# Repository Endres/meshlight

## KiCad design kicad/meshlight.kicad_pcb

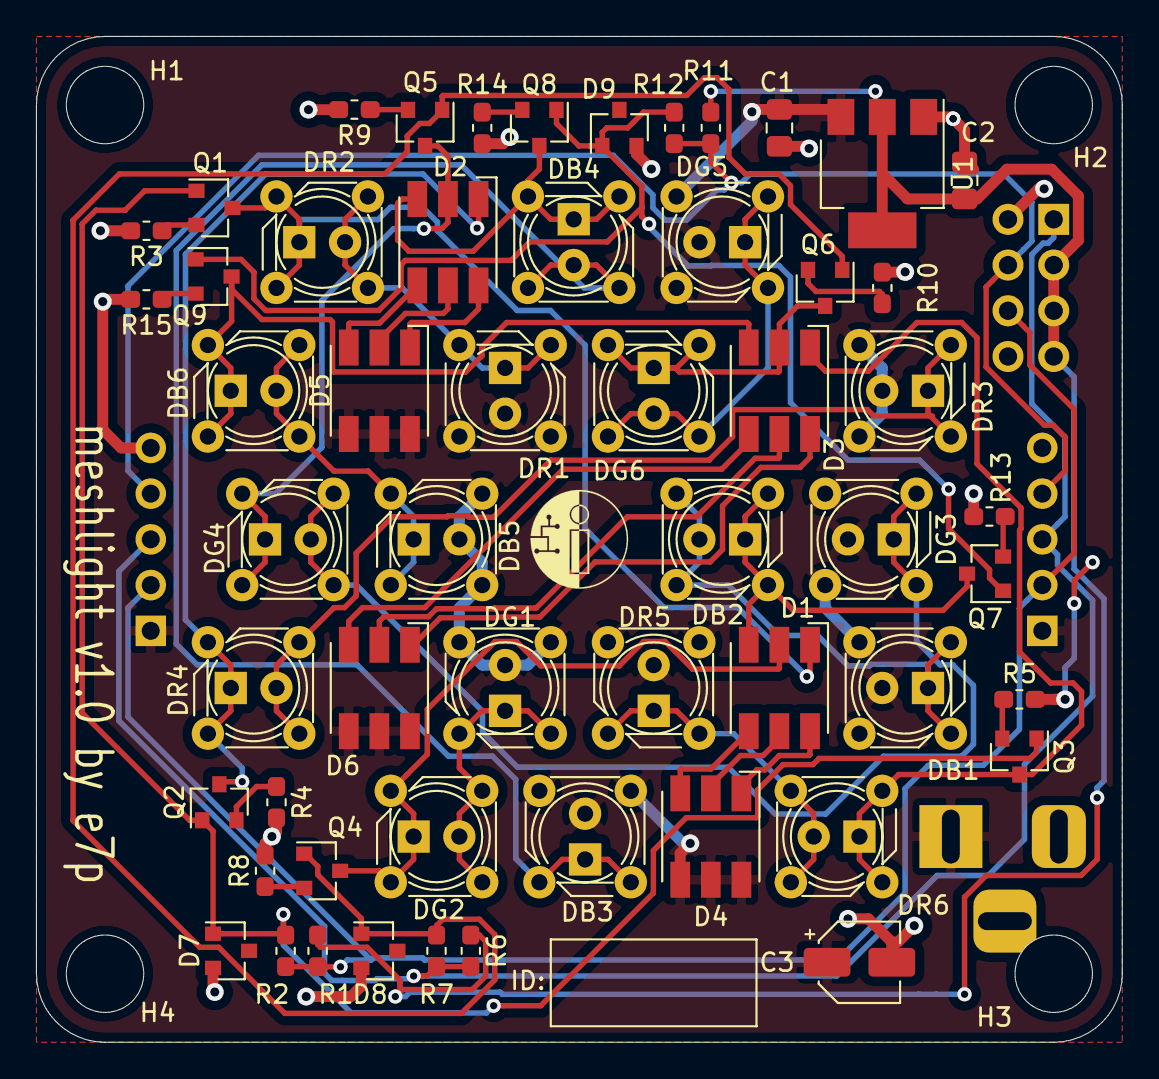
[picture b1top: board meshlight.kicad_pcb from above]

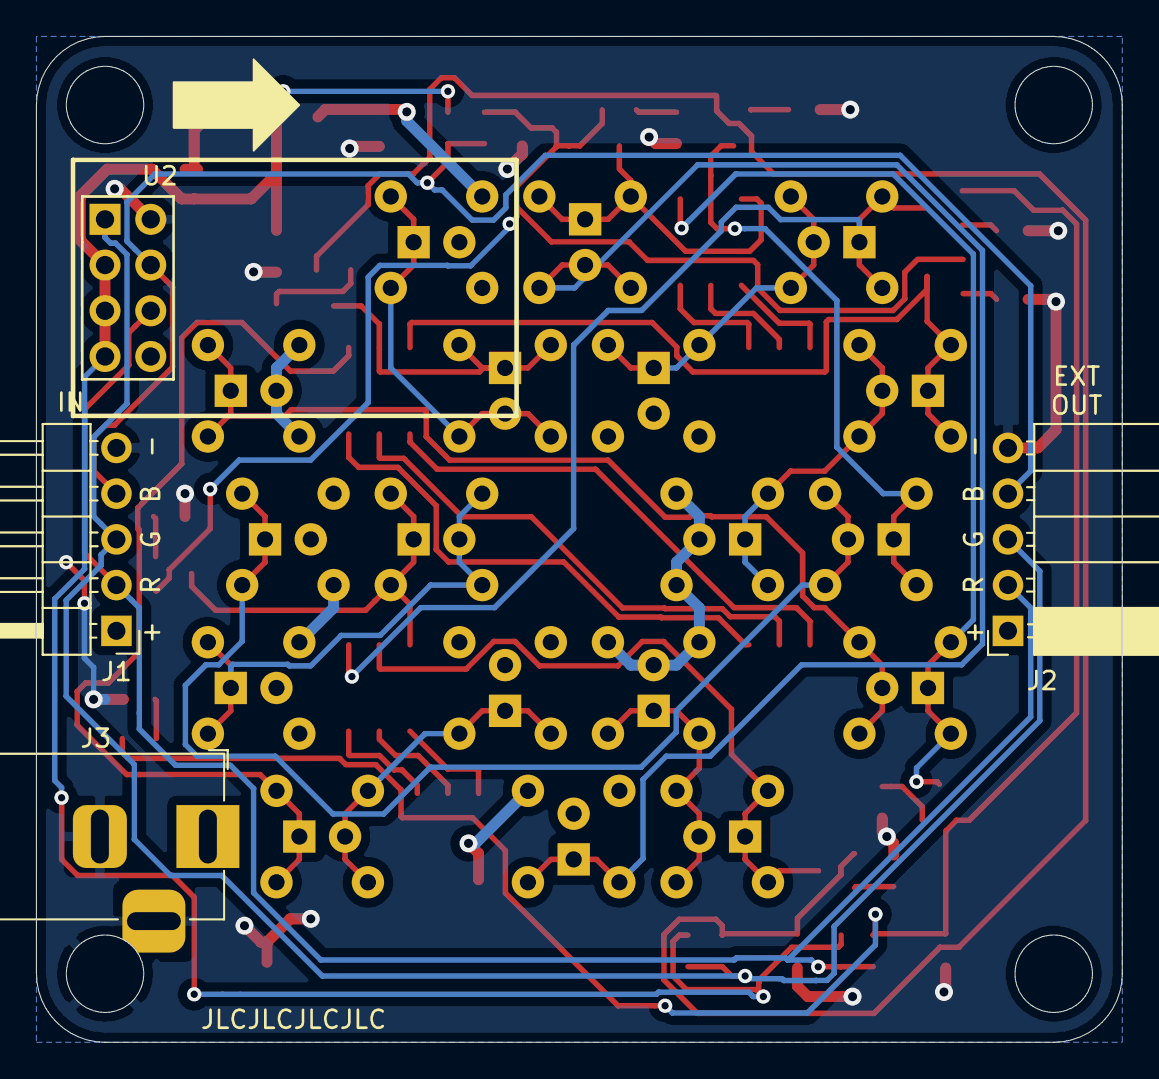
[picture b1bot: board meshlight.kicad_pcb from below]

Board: 2 copper layers, 60.3 x 55.9 mm, 63 parts (4 on the bottom side), 45 nets.

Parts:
C1, C2: 4u7; C_0805_2012Metric_Pad1.15x1.40mm_HandSolder
C3: 10u; CP_Elec_4x5.4
D1, D2, D3, D4, D5, D6: LED_RGB; LED_RGB_5050-6
D7, D8, D9: BAV99; SOT-23
DB1, DB2, DB3, DB4, DB5, DB6: LED; LED_SuperFlux_5x5_4pin_D5.00mm_combi
DG1, DG2, DG3, DG4, DG5, DG6: LED; LED_SuperFlux_5x5_4pin_D5.00mm_combi
DR1, DR2, DR3, DR4, DR5, DR6: LED; LED_SuperFlux_5x5_4pin_D5.00mm_combi
H1, H2, H4: MountingHole; MountingHole_4.3mm_M4
H3: MountingHole_Pad; MountingHole_4.3mm_M4
J1: Conn_01x05_Male; PinHeader_1x05_P2.54mm_Horizontal
J2: Conn_01x05_Female; PinSocket_1x05_P2.54mm_Horizontal
J3: Barrel_Jack_Switch; BarrelJack_Horizontal
Q1, Q2, Q3, Q4, Q5, Q6, Q7, Q8, Q9: BC847; SOT-23
R1, R6, R11: 10k; R_0603_1608Metric_Pad1.05x0.95mm_HandSolder
R2, R7, R12: 1k; R_0603_1608Metric_Pad1.05x0.95mm_HandSolder
R3, R4, R5, R8, R9, R10, R13, R14, R15: 42R2; R_0603_1608Metric_Pad1.05x0.95mm_HandSolder
U1: AP1117-33; SOT-223-3_TabPin2
U2: ESP-01v090; ESP-01

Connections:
+3V3: C2.1, R1.1, R6.1, R11.1, U1.2, U2.3, U2.5, U2.7
+7.5V: C1.2, C3.1, D4.4, D4.5, D4.6, D5.4, D5.5, D5.6, D6.4, D6.5, D6.6, DB1.2, DB3.2, DB5.2, DG1.2, DG3.2, DG5.2, DR1.2, DR3.2, DR5.2, J1.1, J2.1, J3.1, U1.3
/LB1: D1.3, DB2.1, Q7.3
/LB2: D2.3, DB4.1, Q8.3
/LB3: D3.3, DB6.1, Q9.3
/LED_B: J1.4, J2.4, R11.2, R12.1, U2.4
/LED_G: J1.3, J2.3, R6.2, R7.1, U2.1
/LED_R: J1.2, J2.2, R1.2, R2.1, U2.6
/LG1: D1.2, DG2.1, Q4.3
/LG2: D2.2, DG4.1, Q5.3
/LG3: D3.2, DG6.1, Q6.3
/LR1: D1.1, DR2.1, Q1.3
/LR2: D2.1, DR4.1, Q2.3
/LR3: D3.1, DR6.1, Q3.3
GND: C1.1, C2.2, C3.2, D7.2, D8.2, D9.2, H3.1, J1.5, J2.5, J3.2, J3.3, R3.2, R4.2, R5.2, R8.2, R9.2, R10.2, R13.2, R14.2, R15.2, U1.1, U2.2
unnamed: D1.4, D4.3
unnamed: D1.5, D4.2
unnamed: D1.6, D4.1
unnamed: D2.4, D5.3
unnamed: D2.5, D5.2
unnamed: D2.6, D5.1
unnamed: D3.4, D6.3
unnamed: D3.5, D6.2
unnamed: D3.6, D6.1
unnamed: D7.1, Q1.1, Q2.1, Q3.1, R2.2
unnamed: D8.1, Q4.1, Q5.1, Q6.1, R7.2
unnamed: D9.1, Q7.1, Q8.1, Q9.1, R12.2
unnamed: DB1.1, DB2.2
unnamed: DB3.1, DB4.2
unnamed: DB5.1, DB6.2
unnamed: DG1.1, DG2.2
unnamed: DG3.1, DG4.2
unnamed: DG5.1, DG6.2
unnamed: DR1.1, DR2.2
unnamed: DR3.1, DR4.2
unnamed: DR5.1, DR6.2
unnamed: Q1.2, R3.1
unnamed: Q2.2, R4.1
unnamed: Q3.2, R5.1
unnamed: Q4.2, R8.1
unnamed: Q5.2, R9.1
unnamed: Q6.2, R10.1
unnamed: Q7.2, R13.1
unnamed: Q8.2, R14.1
unnamed: Q9.2, R15.1

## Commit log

2020-01-24 First Schematic Draft
2020-01-24 adding white LED channel
2020-01-25 removed the white channel again, but added 6-pin RGB LEDs as an alternative and connectors for expanding multiple PCBs
2020-01-25 fixed ERC bugs
2020-01-26 first placement idea of leds
2020-01-26 basic rough placing of all components
2020-01-26 routed pcb
2020-01-27 added gerber files for fab
2020-01-27 add notes for led selection
2020-01-27 rudimentary starter web interface and notes for implementation
2020-01-28 added first animation and base of the animation collection as well as implemented the timeframerunner completely
2020-02-03 minor modifications and added painlessmesh notes
2020-02-03 translated the painlessmesh demo script from D language to python
2020-02-03 painlessmesh note
2020-02-03 work on the animation provider and adding another basic animation
2020-02-04 first mesh test
2020-02-05 simple UDP implementation (however currently without mesh because of problems)
2020-02-05 implement OTA on nodes and some timeout / connection loss handling
2020-02-10 connection retry attempts for the basic server
2020-02-11 current animation framework state, has to be improved
2020-02-11 current state of frontend template and some notes
2020-02-11 config update
2020-02-11 Event notes
2020-02-12 Treppenblink animation from labor added https://github.com/das-labor/legacy/blob/master/microcontroller/src-atmel/automatization2.0/treppenblink/trunk/animationen.c
2020-02-14 first implementations of AnimationSequence
2020-02-16 sequence table of web interface and server features
2020-02-25 web frontend adapts to received option data completely
2020-02-26 enable frontend to send the animation mode
2020-02-26 external javascript file
2020-02-27 let the frontend receive the current mode as well
2020-03-01 color picker now working
2020-03-02 add global blackout switch
2020-03-02 API fix in blackout
2020-03-04 fix bug in arduino code
2020-03-04 correct property handling of server and frontend
2020-03-04 MAC / ID order of exh ESP8266 modules
2020-03-04 remove obsolete todos from js file
2020-03-14 event system developed, however the AnimationSequence class needs still to be overworked. AnimationCollection was integrated into AnimationSequence
2020-03-14 exh config
